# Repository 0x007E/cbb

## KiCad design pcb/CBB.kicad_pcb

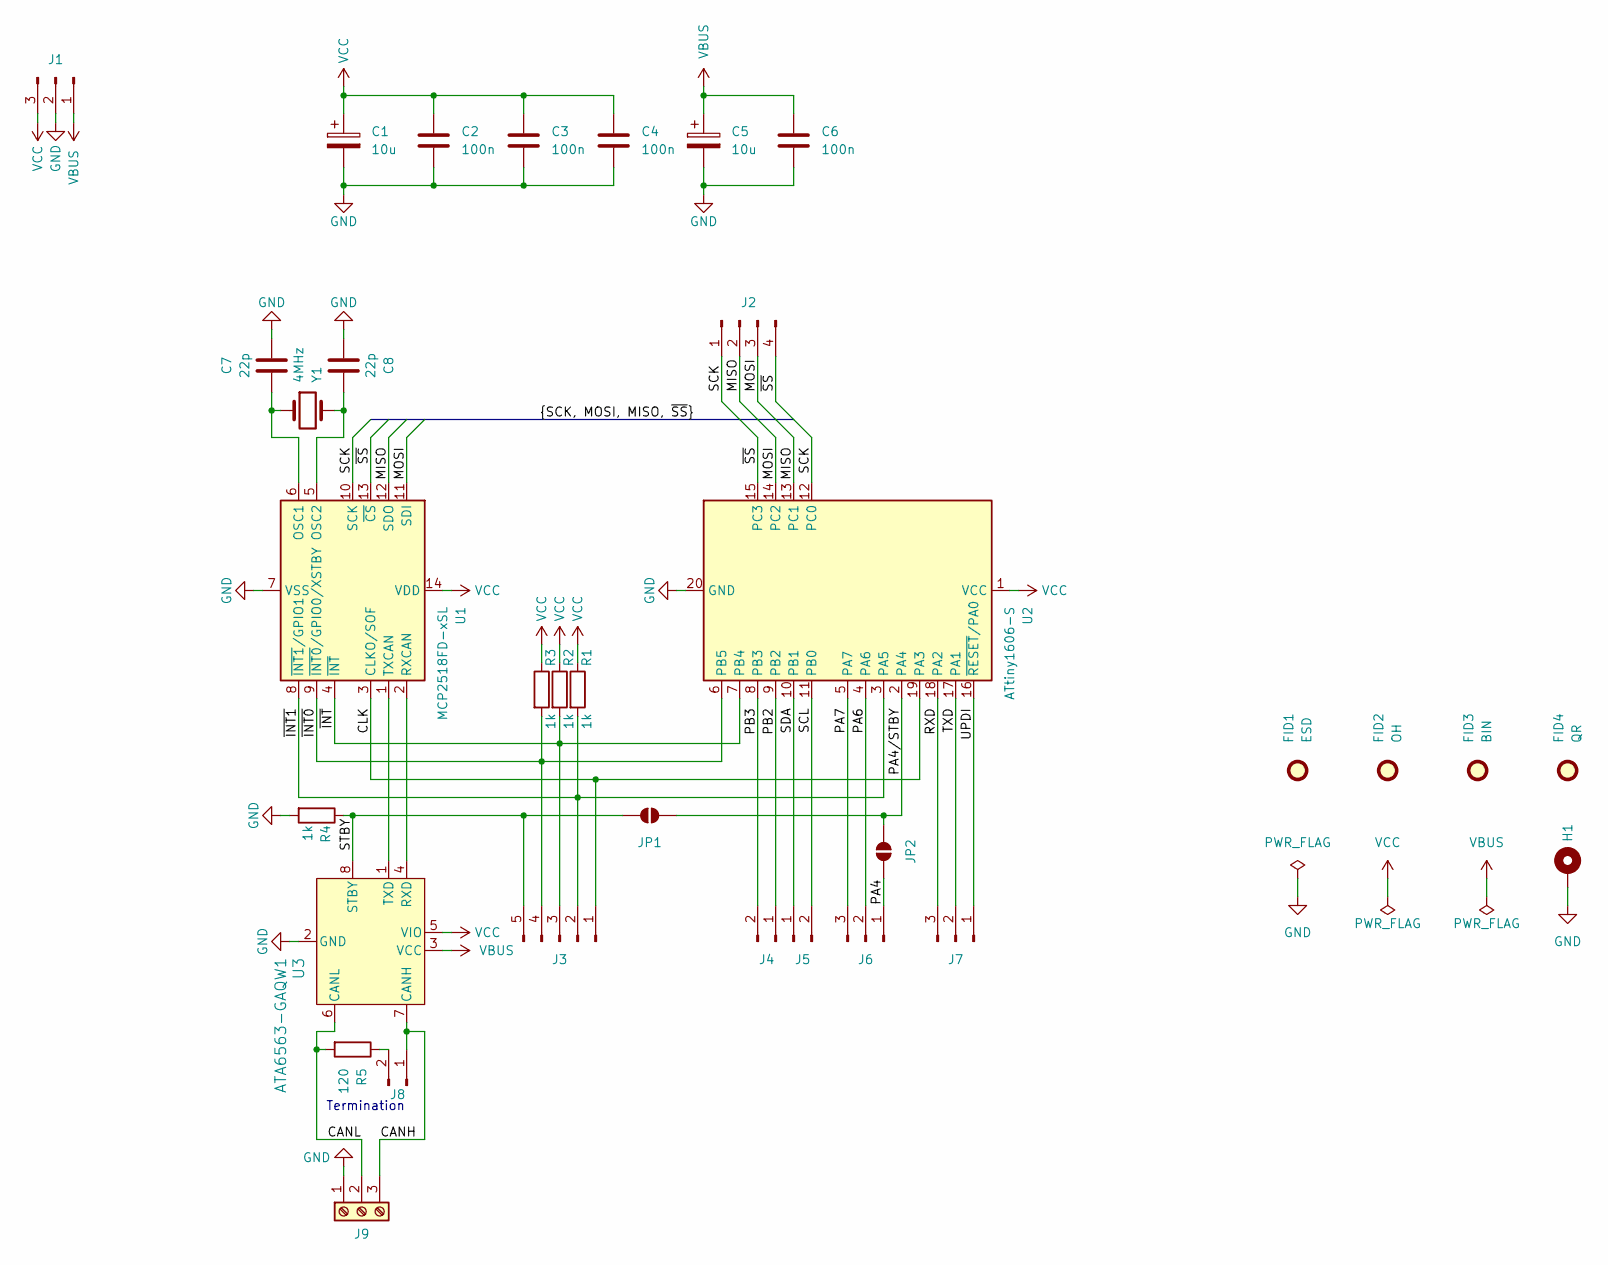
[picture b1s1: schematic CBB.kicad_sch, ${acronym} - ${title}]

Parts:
C1, C5: 10u; CP_EIA-3528-21_Kemet-B
C2, C3, C4, C6: 100n; C_1206_3216Metric
C7, C8: 22p; C_1206_3216Metric
FID1: ESD; ESD-Logo_6.6x6mm_SilkScreen
FID2: OH; OSHW-Logo_5.7x6mm_SilkScreen
FID3: BIN; WEEE-Logo_4.2x6mm_SilkScreen
FID4: QR; QR_0x007e_very_small
H1: MountingHole_Pad; MountingHole_3.2mm_M3_DIN965_Pad
J1, J6, J7: Conn_01x03_Pin; PinHeader_1x03_P2.54mm_Vertical
J2: Conn_01x04_Pin; PinHeader_1x04_P2.54mm_Vertical
J3: Conn_01x05_Pin; PinHeader_1x05_P2.54mm_Vertical
J4, J5, J8: Conn_01x02_Pin; PinHeader_1x02_P2.54mm_Vertical
J9: Screw_Terminal_01x03; PhoenixContact_MSTBA_2,5_3-G-5,08_1x03_P5.08mm_Horizontal; DigiKey 277-1107-ND, 277-1012-ND
JP1, JP2: SolderJumper_2_Open; SolderJumper-2_P1.3mm_Open_RoundedPad1.0x1.5mm
R1, R2, R3, R4: 1k; R_1206_3216Metric
R5: 120; R_1206_3216Metric
U1: MCP2518FD-xSL; SOIC-14_3.9x8.7mm_P1.27mm; DigiKey MCP2518FDT-E/SLCT-ND
U2: ATtiny1606-S; SOIC-20W_7.5x12.8mm_P1.27mm
U3: ATA6563-GAQW1; SOIC-8_3.9x4.9mm_P1.27mm; DigiKey 150-ATA6563-GAQW1CT-ND
Y1: 4MHz; Crystal_SMD_HC49-SD; DigiKey 1908-J49SMH-A-G-G-K-4M0CT-ND

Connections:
/CANH: J8.1, J9.3, U3.7 (CANH)
/CANL: J9.2, R5.2, U3.6 (CANL)
/CLK: J3.1, U1.3 (CLKO/SOF), U2.19 (PA3)
/MISO: J2.2, U1.12 (SDO), U2.13 (PC1)
/MOSI: J2.3, U1.11 (SDI), U2.14 (PC2)
/PA4: J6.1, JP2.2 (B)
/PA4/STBY: JP1.1 (A), JP2.1 (A), U2.2 (PA4)
/PA6: J6.2, U2.4 (PA6)
/PA7: J6.3, U2.5 (PA7)
/PB2: J4.1, U2.9 (PB2)
/PB3: J4.2, U2.8 (PB3)
/RXD: J7.3, U2.18 (PA2)
/SCK: J2.1, U1.10 (SCK), U2.12 (PC0)
/SCL: J5.2, U2.11 (PB0)
/SDA: J5.1, U2.10 (PB1)
/STBY: J3.5, JP1.2 (B), R4.1, U3.8 (STBY)
/TXD: J7.2, U2.17 (PA1)
/UPDI: J7.1, U2.16 (~RESET/PA0)
/~INT0: J3.4, R3.2, U1.9 (~INT0/GPIO0/XSTBY), U2.6 (PB5)
/~INT1: J3.2, R1.2, U1.8 (~INT1/GPIO1), U2.3 (PA5)
/~INT: J3.3, R2.2, U1.4 (~INT), U2.7 (PB4)
/~SS: J2.4, U1.13 (~CS), U2.15 (PC3)
GND: C1.2, C2.2, C3.2, C4.2, C5.2, C6.2, C7.1, C8.1, H1.1, J1.2, J9.1, R4.2, U1.7 (VSS), U2.20 (GND), U3.2 (GND)
unnamed: J8.2, R5.1
unnamed: C7.2, U1.6 (OSC1), Y1.1
unnamed: C8.2, U1.5 (OSC2), Y1.2
unnamed: U1.2 (RXCAN), U3.4 (RXD)
unnamed: U1.1 (TXCAN), U3.1 (TXD)
VBUS: C5.1, C6.1, J1.1, U3.3 (VCC)
VCC: C1.1, C2.1, C3.1, C4.1, J1.3, R1.1, R2.1, R3.1, U1.14 (VDD), U2.1 (VCC), U3.5 (VIO)

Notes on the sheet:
Termination

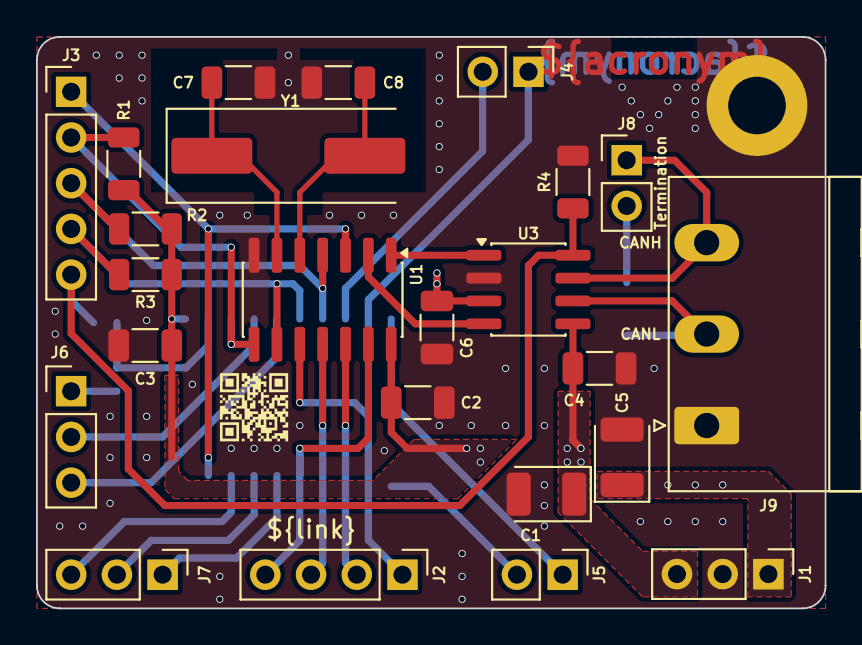
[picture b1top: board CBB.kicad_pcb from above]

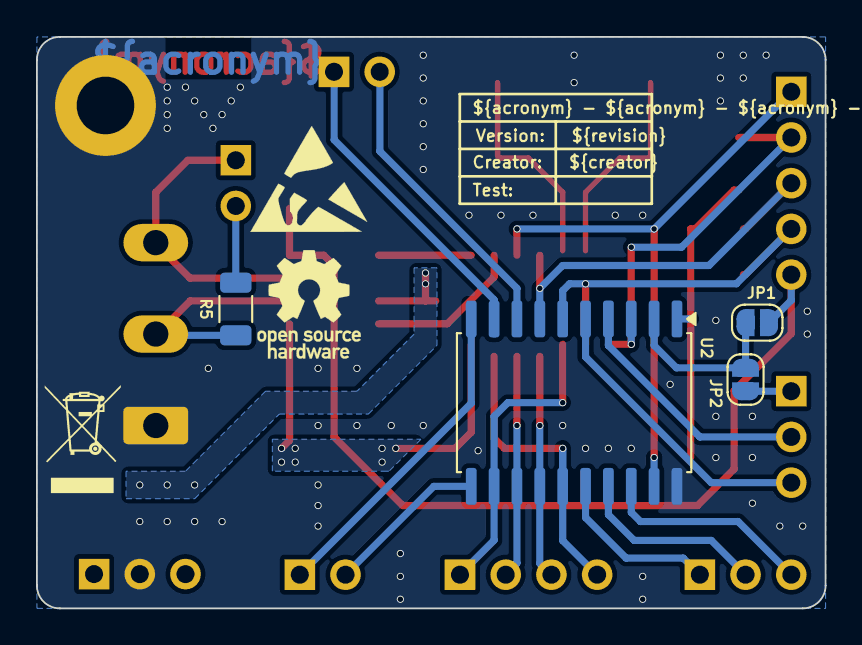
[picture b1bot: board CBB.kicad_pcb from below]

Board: 2 copper layers, 43.8 x 31.8 mm, 33 parts (7 on the bottom side), 30 nets.

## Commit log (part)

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2026-05-15 Add pcb layout

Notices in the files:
parts and their libraries:
license: CC BY-NC-SA 4.0
